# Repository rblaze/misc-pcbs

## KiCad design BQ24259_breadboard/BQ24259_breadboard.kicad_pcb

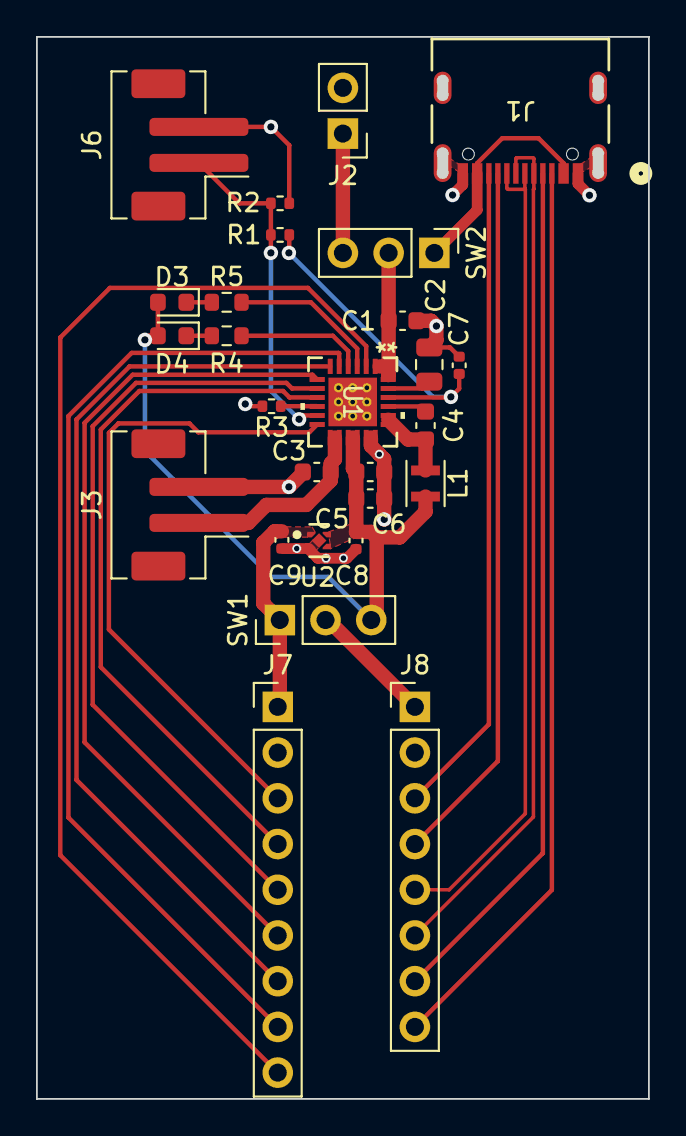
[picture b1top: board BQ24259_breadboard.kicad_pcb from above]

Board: 2 copper layers, 34.0 x 59.0 mm, 27 parts (0 on the bottom side), 31 nets.

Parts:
C1: 1u; C_0603_1608Metric
C2: 22u; C_0805_2012Metric
C3, C5, C6: 10u; C_0603_1608Metric
C4: 47n; C_0603_1608Metric
C7: 4u7; C_0402_1005Metric
C8, C9: 1u; C_0402_1005Metric
D3: Green; LED_0603_1608Metric
D4: Yellow; LED_0603_1608Metric
J1: USB_C_Receptacle_USB2.0; USB4105_GCT
J2: Power_In; PinHeader_1x02_P2.54mm_Vertical
J3: Battery; JST_PH_B2B-PH-SM4-TB_1x02-1MP_P2.00mm_Vertical
J6: BatTemp; JST_PH_B2B-PH-SM4-TB_1x02-1MP_P2.00mm_Vertical
J7: BB_Right; PinHeader_1x09_P2.54mm_Vertical
J8: BB_Left; PinHeader_1x08_P2.54mm_Vertical
L1: 1u; L_Murata_DFE201610P
R1: 5k25; R_0402_1005Metric
R2: 31k23; R_0402_1005Metric
R3: 220; R_0402_1005Metric
R4, R5: 220; R_0603_1608Metric
SW1: SW_OUT; PinHeader_1x03_P2.54mm_Vertical
SW2: SW_SRC; PinHeader_1x03_P2.54mm_Vertical
U1: BQ24259RGER; RGE24_2P7X2P7_TEX
U2: TPS7A2033PDQNR; DQN0004A-MFG

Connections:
+3V3: C9.1, J7.1, SW1.1 (A), U2.1 (OUT)
/EXT_VBUS: J2.1, SW2.3 (C)
/QON: J7.3, U1.12 (QON)
/USB_D+: J1.A6 (D+), J1.B6 (D+), J8.5
/USB_D-: J1.A7 (D-), J1.B7 (D-), J8.6
/USB_VBUS: J1.A4-B9, J1.B4-A9, SW2.1 (A)
/VBAT: C3.1, J3.1, U1.13 (BAT), U1.14 (BAT)
/VBUS: C1.2, SW2.2 (B), U1.1 (VBUS), U1.24 (VBUS)
/VSYS: C5.2, C6.2, C8.2, D3.2 (A), D4.2 (A), L1.2, SW1.3 (C), U1.15 (SYS), U1.16 (SYS), U2.3 (EN), U2.4 (IN)
GND: C1.1, C2.1, C3.2, C5.1, C6.1, C7.2, C8.1, C9.2, J1.15, J1.16, J1.A1-B12, J1.B1-A12, J2.2, J3.2, J6.2, J7.2, J8.2, R2.2, R3.2, U1.17 (PGND), U1.18 (PGND), U1.25 (EPAD), U1.V, U2.2 (GND), U2.5 (Thermal_Pad)
unnamed: C4.1, L1.1, U1.19 (SW), U1.20 (SW)
unnamed: D3.1 (K), R5.1
unnamed: D4.1 (K), R4.1
unnamed: J1.A5 (CC1), J8.7
unnamed: J1.B5 (CC2), J8.3
unnamed: J1.A8 (SBU1), J8.4
unnamed: J1.B8 (SBU2), J8.8
unnamed: J6.1, R1.2, R2.1, U1.11 (TS)
unnamed: J7.4, U1.9 (~CE)
unnamed: J7.5, U1.8 (OTG)
unnamed: J7.6, U1.7 (INT)
unnamed: J7.7, U1.6 (SDA)
unnamed: J7.8, U1.5 (SCL)
unnamed: J7.9, U1.2 (PSEL)
unnamed: C4.2, U1.21 (BTST)
unnamed: R3.1, U1.10 (ILIM)
unnamed: C2.2, U1.23 (PMID)
unnamed: C7.1, R1.1, U1.22 (REGN)
unnamed: R4.2, U1.4 (STAT)
unnamed: R5.2, U1.3 (~PG)
VDD: J8.1, SW1.2 (B)
